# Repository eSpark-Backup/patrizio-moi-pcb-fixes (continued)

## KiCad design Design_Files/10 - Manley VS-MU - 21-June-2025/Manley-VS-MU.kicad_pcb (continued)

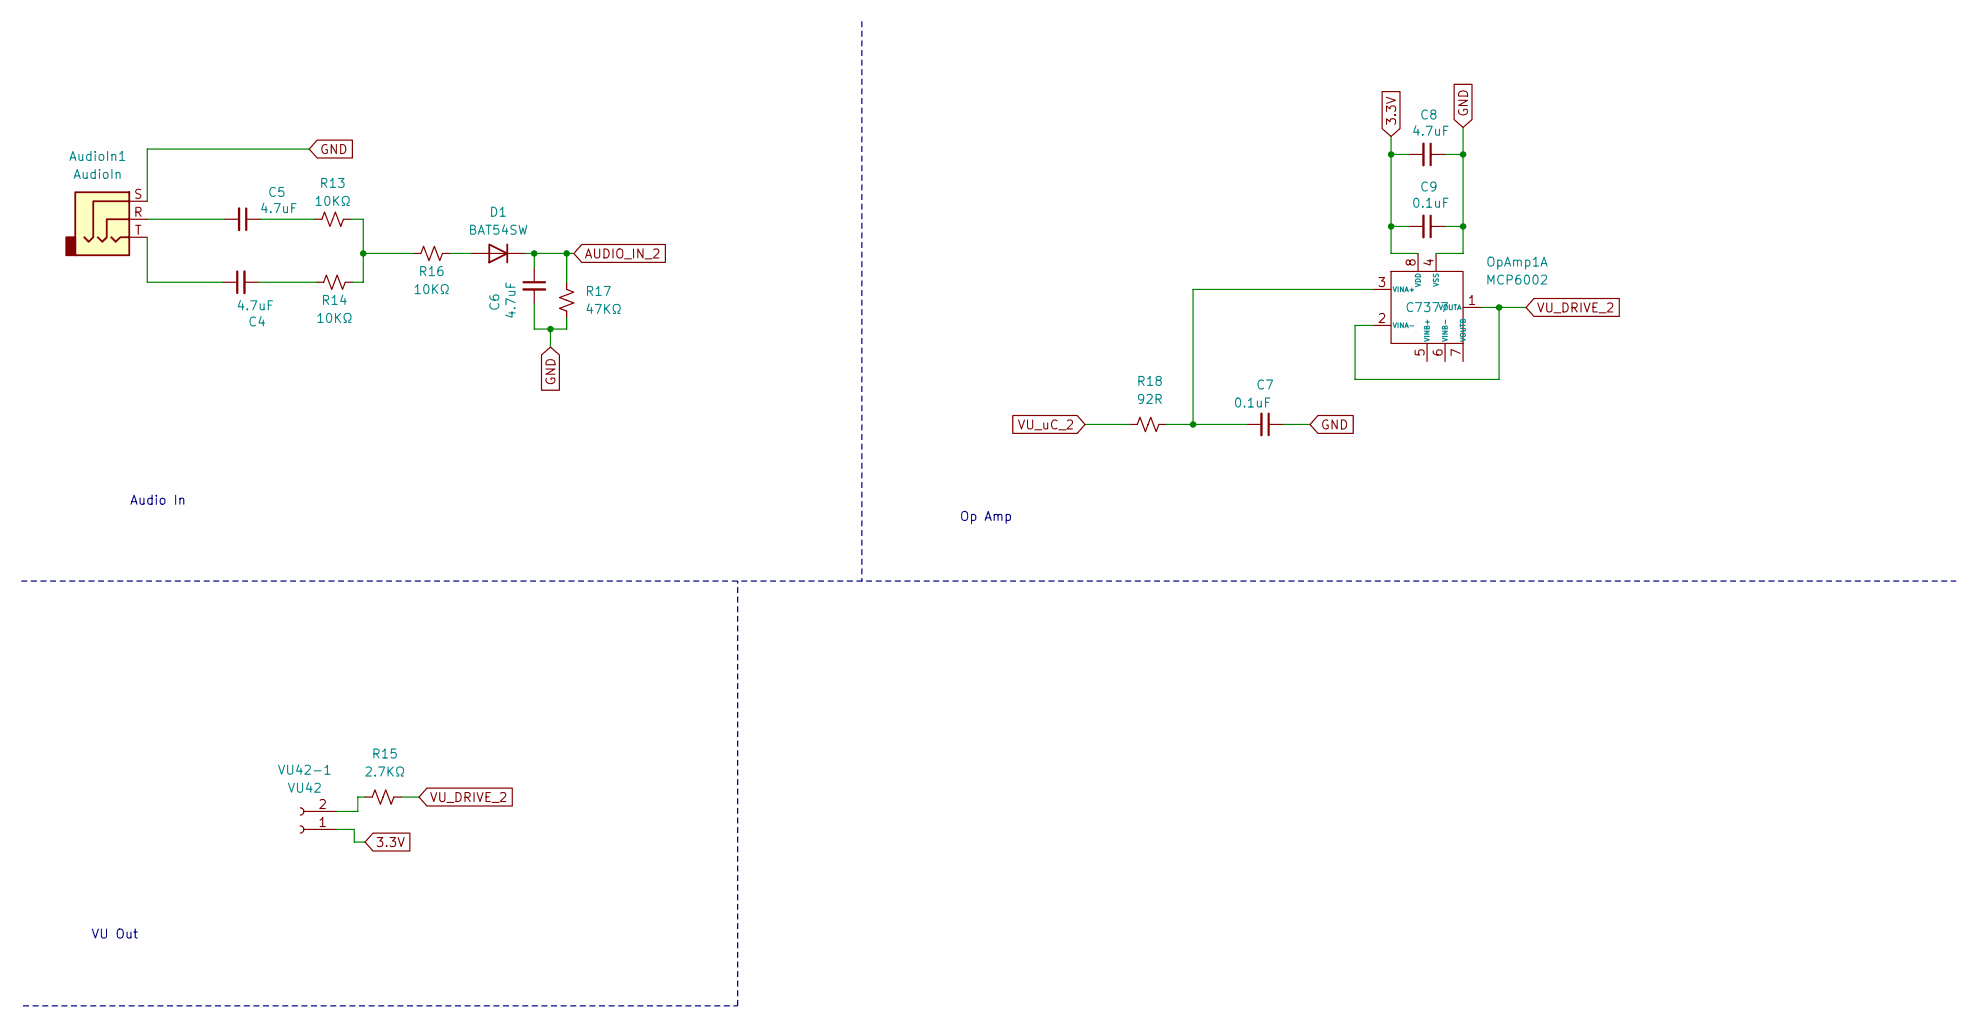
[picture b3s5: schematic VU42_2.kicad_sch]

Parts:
AudioIn1: AudioIn; Jack_3.5mm_PJ320D_Horizontal; LCSC Part Number C22459515
C4, C5, C6, C8: 4.7uF; C_0402_1005Metric; LCSC Part Number C23733
C7: 0.1uF; C_0402_1005Metric
C9: 0.1uF; C_0402_1005Metric; LCSC Part Number C1525
D1: BAT54SW; D_SOD-323; LCSC Part Number C27636114
OpAmp1: MCP6002; SOIC-8_3.9x4.9mm_P1.27mm; LCSC Part Number C7377
R13, R14, R16: 10KΩ; R_0402_1005Metric; LCSC Part Number C25744
R15: 2.7KΩ; R_0603_1608Metric; LCSC Part Number C13167
R17: 47KΩ; R_0402_1005Metric; LCSC Part Number C25792
R18: 92R; R_0402_1005Metric
VU42-1: VU42; PinSocket_1x02_P2.54mm_Vertical

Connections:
3.3V: C8.2, C9.2, OpAmp1.8 (VDD), VU42-1.1; also elsewhere on the board
AUDIO_IN_2: C6.1, D1.1 (K), R17.2; also elsewhere on the board
GND: AudioIn1.S, C6.2, C7.1, C8.1, C9.1, OpAmp1.4 (VSS), R17.1; also elsewhere on the board
unnamed: AudioIn1.R, C5.2
unnamed: AudioIn1.T, C4.1
unnamed: C4.2, R14.2
unnamed: C5.1, R13.2
unnamed: D1.2 (A), R16.1
unnamed: C7.2, OpAmp1.3 (VINA+), R18.1
unnamed: R13.1, R14.1, R16.2
unnamed: R15.2, VU42-1.2
VU_DRIVE_2: OpAmp1.1 (VOUTA), OpAmp1.2 (VINA-), R15.1
VU_uC_2: R18.2; also elsewhere on the board

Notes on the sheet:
VU Out
Op Amp
Audio In

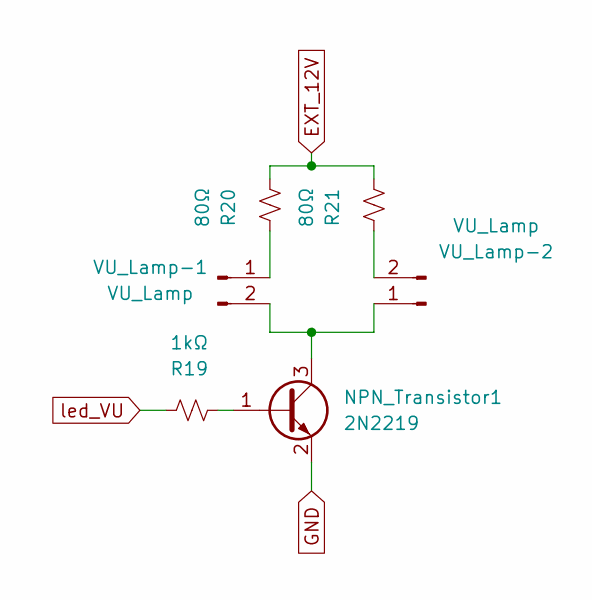
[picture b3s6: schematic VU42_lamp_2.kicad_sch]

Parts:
NPN_Transistor1: 2N2219; SOT-23; LCSC Part Number C2150
R19: 1kΩ; R_0402_1005Metric; Manufacturer_Part_Number 0402WGF3300TCE; LCSC Part Number C11702
R20, R21: 80Ω; R_0402_1005Metric; Manufacturer_Part_Number RT0402FRE0780RL; LCSC Part Number C854436
VU_Lamp-1, VU_Lamp-2: VU_Lamp; PinSocket_1x02_P2.54mm_Vertical

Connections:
EXT_12V: R20.1, R21.1; also elsewhere on the board
GND: NPN_Transistor1.2 (E); also elsewhere on the board
unnamed: NPN_Transistor1.1 (B), R19.1
unnamed: NPN_Transistor1.3 (C), VU_Lamp-1.2, VU_Lamp-2.1
unnamed: R20.2, VU_Lamp-1.1
unnamed: R21.2, VU_Lamp-2.2
led_VU: R19.2; also elsewhere on the board

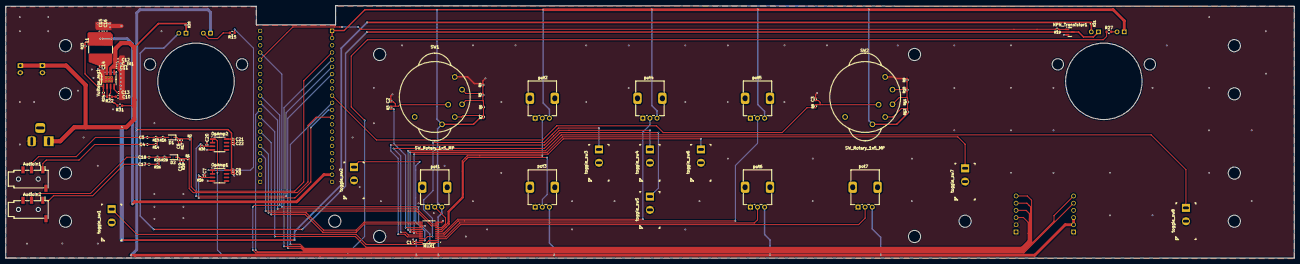
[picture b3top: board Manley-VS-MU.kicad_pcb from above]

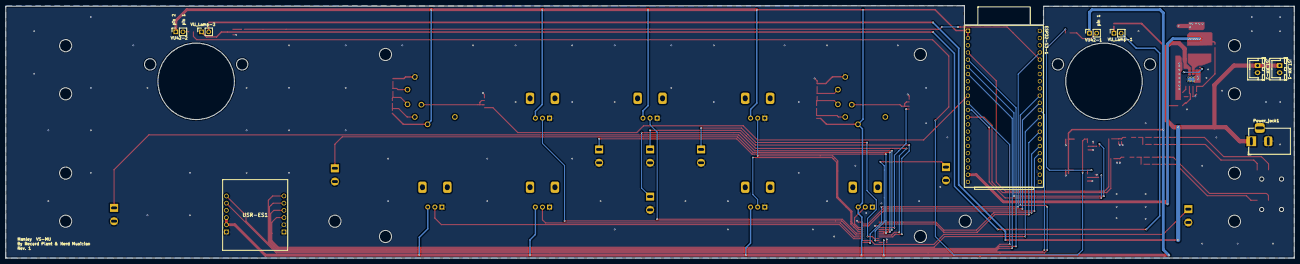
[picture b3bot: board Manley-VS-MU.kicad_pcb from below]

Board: 2 copper layers, 455.0 x 89.1 mm, 90 parts (9 on the bottom side), 76 nets.

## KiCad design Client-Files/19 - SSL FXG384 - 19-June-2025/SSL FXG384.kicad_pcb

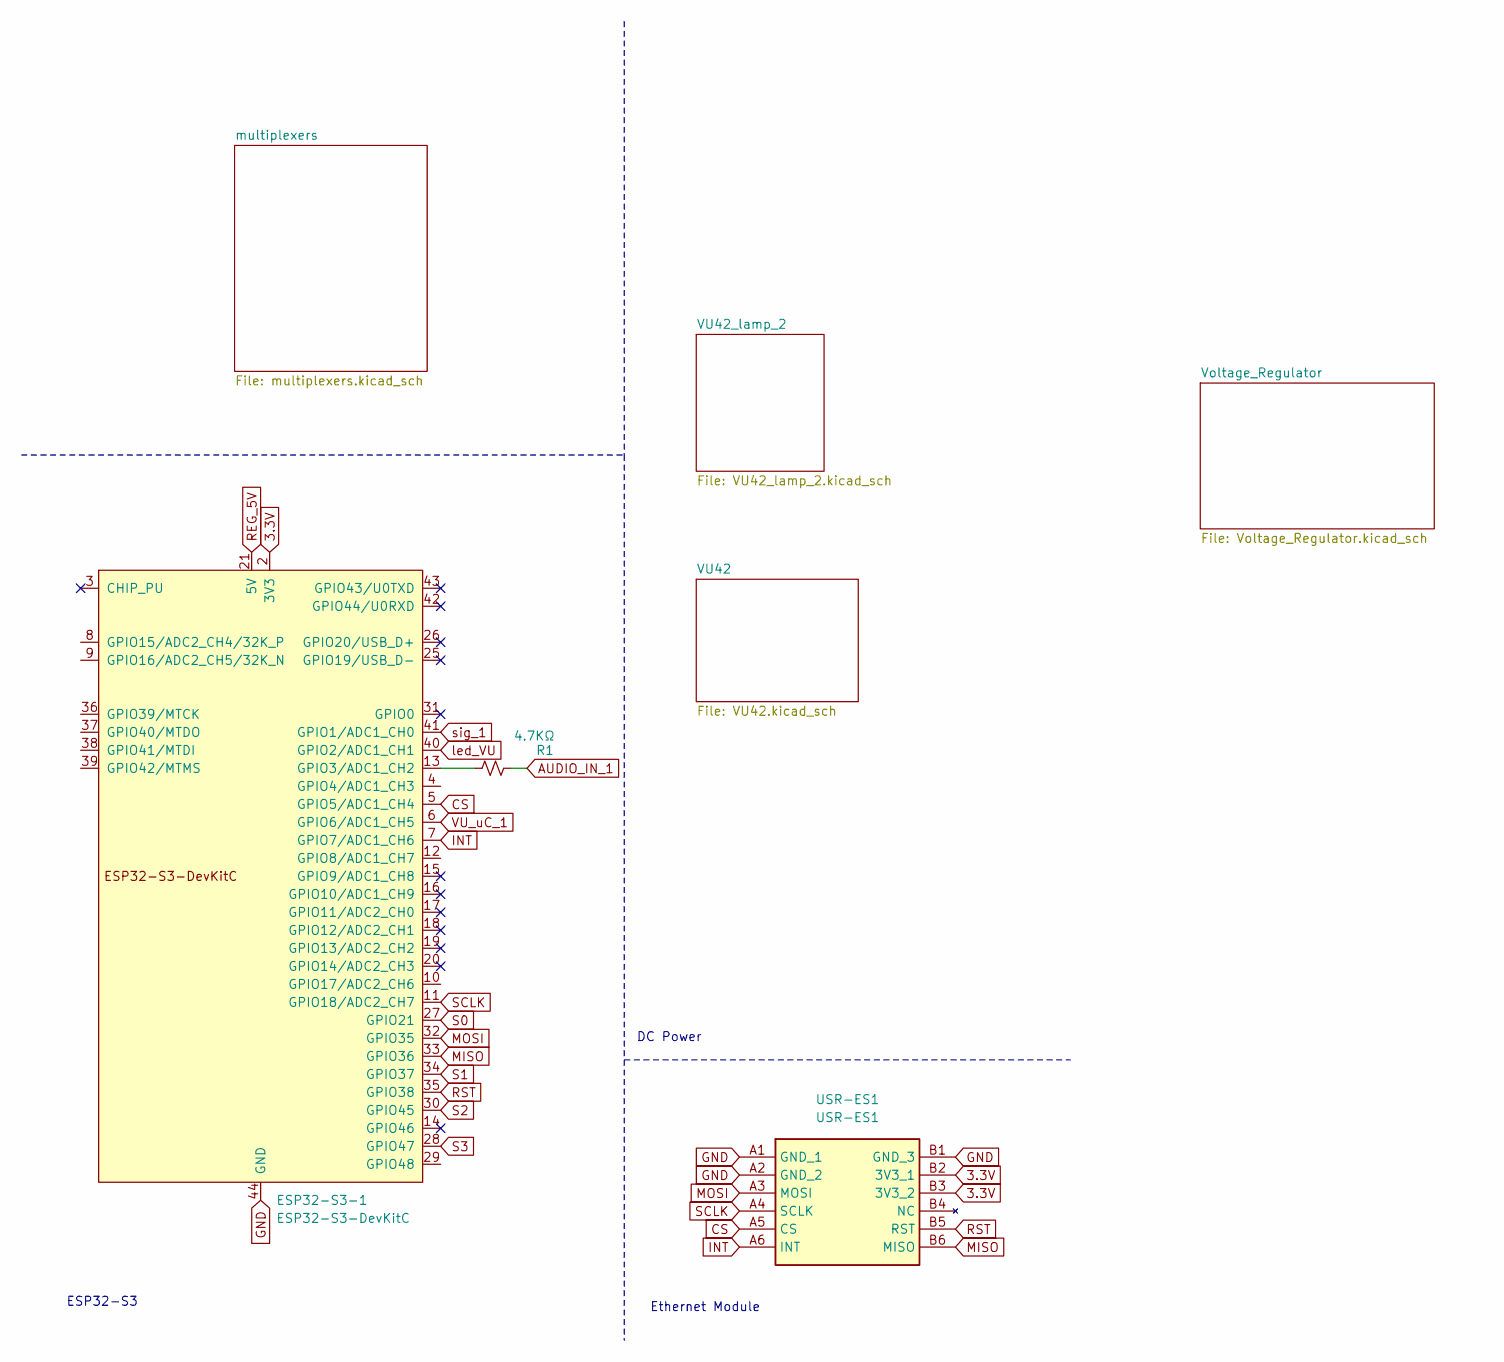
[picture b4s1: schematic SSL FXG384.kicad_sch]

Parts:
ESP32-S3-1: ESP32-S3-DevKitC; ESP32-S3-DEVKITC-1-N8R2-2
R1: 4.7KΩ; R_0402_1005Metric; LCSC Part Number C25900
USR-ES1: USR-ES1; USRES1; Manufacturer_Part_Number USR-ES1

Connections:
3.3V: ESP32-S3-1.1 (3V3), ESP32-S3-1.2 (3V3), USR-ES1.B2 (3V3_1), USR-ES1.B3 (3V3_2); also elsewhere on the board
AUDIO_IN_1: R1.1; also elsewhere on the board
CS: ESP32-S3-1.5 (GPIO5/ADC1_CH4), USR-ES1.A5 (CS)
GND: ESP32-S3-1.22 (GND), ESP32-S3-1.23 (GND), ESP32-S3-1.24 (GND), ESP32-S3-1.44 (GND), USR-ES1.A1 (GND_1), USR-ES1.A2 (GND_2), USR-ES1.B1 (GND_3); also elsewhere on the board
INT: ESP32-S3-1.7 (GPIO7/ADC1_CH6), USR-ES1.A6 (INT)
MISO: ESP32-S3-1.33 (GPIO36), USR-ES1.B6 (MISO)
MOSI: ESP32-S3-1.32 (GPIO35), USR-ES1.A3 (MOSI)
unnamed: ESP32-S3-1.13 (GPIO3/ADC1_CH2), R1.2
REG_5V: ESP32-S3-1.21 (5V); also elsewhere on the board
RST: ESP32-S3-1.35 (GPIO38), USR-ES1.B5 (RST)
S0: ESP32-S3-1.27 (GPIO21); also elsewhere on the board
S1: ESP32-S3-1.34 (GPIO37); also elsewhere on the board
S2: ESP32-S3-1.30 (GPIO45); also elsewhere on the board
S3: ESP32-S3-1.28 (GPIO47); also elsewhere on the board
SCLK: ESP32-S3-1.11 (GPIO18/ADC2_CH7), USR-ES1.A4 (SCLK)
VU_uC_1: ESP32-S3-1.6 (GPIO6/ADC1_CH5); also elsewhere on the board
led_VU: ESP32-S3-1.40 (GPIO2/ADC1_CH1); also elsewhere on the board
sig_1: ESP32-S3-1.41 (GPIO1/ADC1_CH0); also elsewhere on the board

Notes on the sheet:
Ethernet Module
DC Power
ESP32-S3

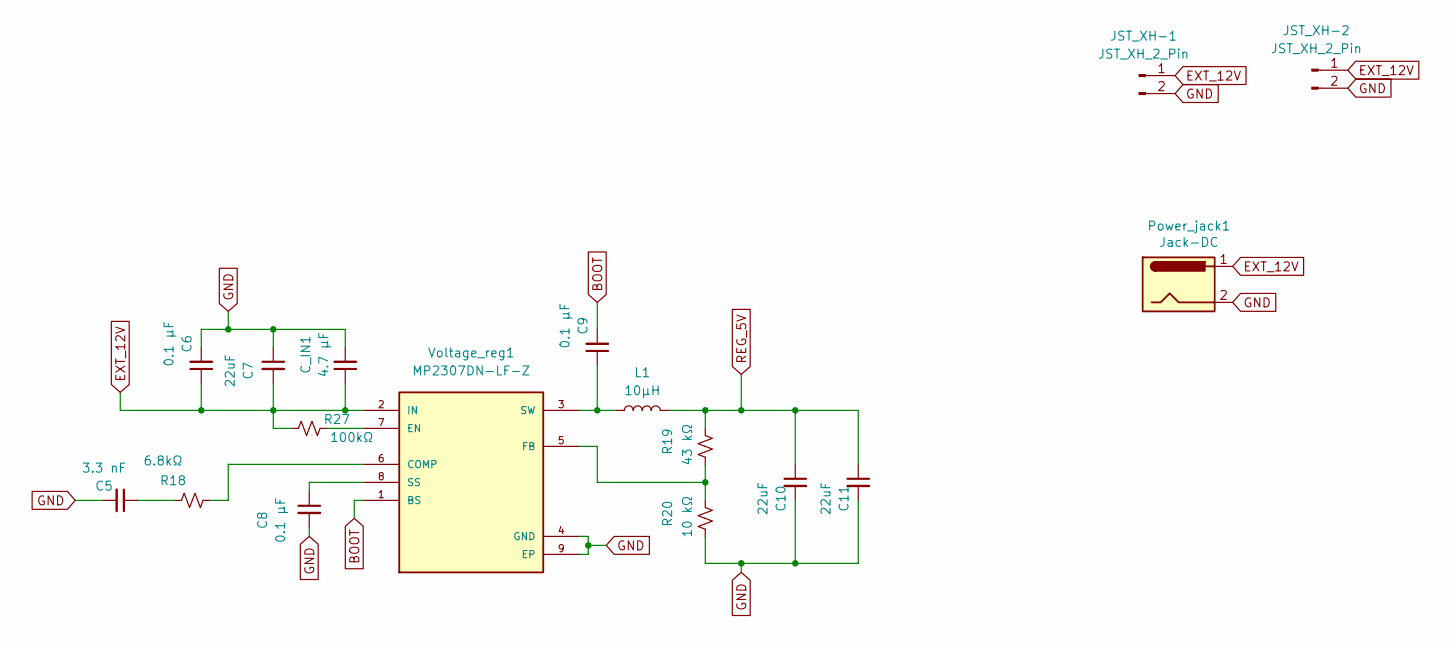
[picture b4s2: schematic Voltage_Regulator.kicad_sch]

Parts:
C5: 3.3 nF; C_0603_1608Metric; LCSC Part Number C1613
C6, C8, C9: 0.1 µF; C_0402_1005Metric; LCSC Part Number C1525
C7, C10, C11: 22uF; C_0603_1608Metric; LCSC Part Number C59461
C_IN1: 4.7 µF; C_0402_1005Metric; LCSC Part Number C23733
JST_XH-1, JST_XH-2: JST_XH_2_Pin; JST_XH_B2B-XH-A_1x02_P2.50mm_Vertical
L1: 10µH; L_Bourns-SRN8040_8x8.15mm; LCSC Part Number C37429
Power_jack1: Jack-DC; BarrelJack_Horizontal
R18: 6.8kΩ; R_0603_1608Metric; LCSC Part Number C23212
R19: 43 kΩ; R_0402_1005Metric; LCSC Part Number C2906943
R20: 10 kΩ; R_0402_1005Metric; LCSC Part Number C25744
R27: 100kΩ; R_0603_1608Metric
Voltage_reg1: MP2307DN-LF-Z; SOIC-8-1EP_3.9x4.9mm_P1.27mm_EP2.29x3mm_ThermalVias; PARTREV 1.9; LCSC Part Number C2928813

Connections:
BOOT: C9.2, Voltage_reg1.1 (BS)
EXT_12V: C6.1, C7.2, C_IN1.1, JST_XH-1.1, JST_XH-2.1, Power_jack1.1, R27.1, Voltage_reg1.2 (IN); also elsewhere on the board
GND: C5.2, C6.2, C7.1, C8.2, C10.2, C11.2, C_IN1.2, JST_XH-1.2, JST_XH-2.2, Power_jack1.2, R20.2, Voltage_reg1.4 (GND), Voltage_reg1.9 (EP); also elsewhere on the board
unnamed: C5.1, R18.1
unnamed: R18.2, Voltage_reg1.6 (COMP)
unnamed: R27.2, Voltage_reg1.7 (EN)
unnamed: R19.2, R20.1, Voltage_reg1.5 (FB)
unnamed: C8.1, Voltage_reg1.8 (SS)
unnamed: C9.1, L1.1, Voltage_reg1.3 (SW)
REG_5V: C10.1, C11.1, L1.2, R19.1; also elsewhere on the board

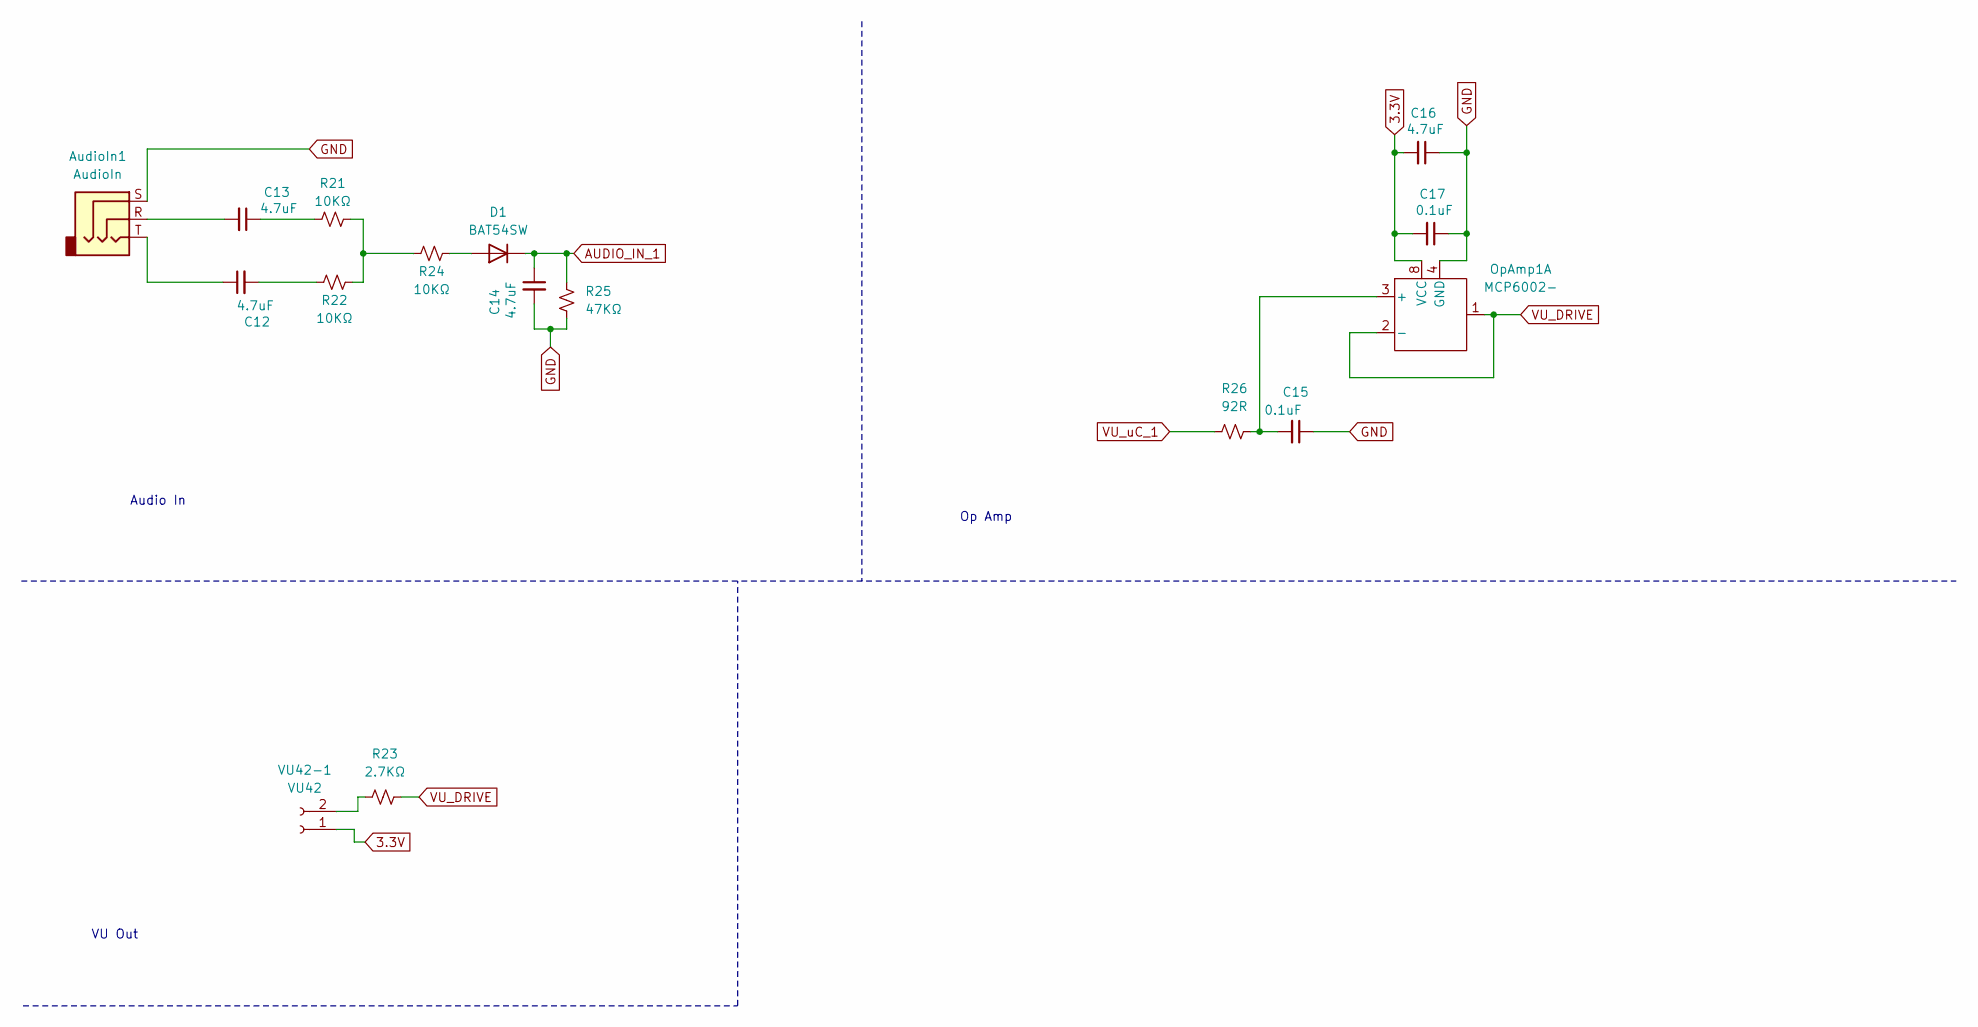
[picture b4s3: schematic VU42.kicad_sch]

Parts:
AudioIn1: AudioIn; Jack_3.5mm_PJ320D_Horizontal; LCSC Part Number C22459515
C12, C13, C14, C16: 4.7uF; C_0402_1005Metric; LCSC Part Number C23733
C15: 0.1uF; C_0402_1005Metric
C17: 0.1uF; C_0402_1005Metric; LCSC Part Number C1525
D1: BAT54SW; D_SOD-323; LCSC Part Number C27636114
OpAmp1: MCP6002-; SOIC-8_3.9x4.9mm_P1.27mm; LCSC Part Number C7377
R21, R22, R24: 10KΩ; R_0402_1005Metric; LCSC Part Number C25744
R23: 2.7KΩ; R_0603_1608Metric; LCSC Part Number C13167
R25: 47KΩ; R_0402_1005Metric; LCSC Part Number C25792
R26: 92R; R_0402_1005Metric
VU42-1: VU42; PinSocket_1x02_P2.54mm_Vertical

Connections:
3.3V: C16.2, C17.2, OpAmp1.8 (VCC), VU42-1.1; also elsewhere on the board
AUDIO_IN_1: C14.1, D1.1 (K), R25.2; also elsewhere on the board
GND: AudioIn1.S, C14.2, C15.1, C16.1, C17.1, OpAmp1.4 (GND), R25.1; also elsewhere on the board
unnamed: AudioIn1.R, C13.2
unnamed: AudioIn1.T, C12.1
unnamed: C12.2, R22.2
unnamed: C13.1, R21.2
unnamed: D1.2 (A), R24.1
unnamed: C15.2, OpAmp1.3 (+), R26.1
unnamed: R21.1, R22.1, R24.2
unnamed: R23.2, VU42-1.2
VU_DRIVE: OpAmp1.1, OpAmp1.2 (-), R23.1
VU_uC_1: R26.2; also elsewhere on the board

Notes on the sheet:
VU Out
Op Amp
Audio In

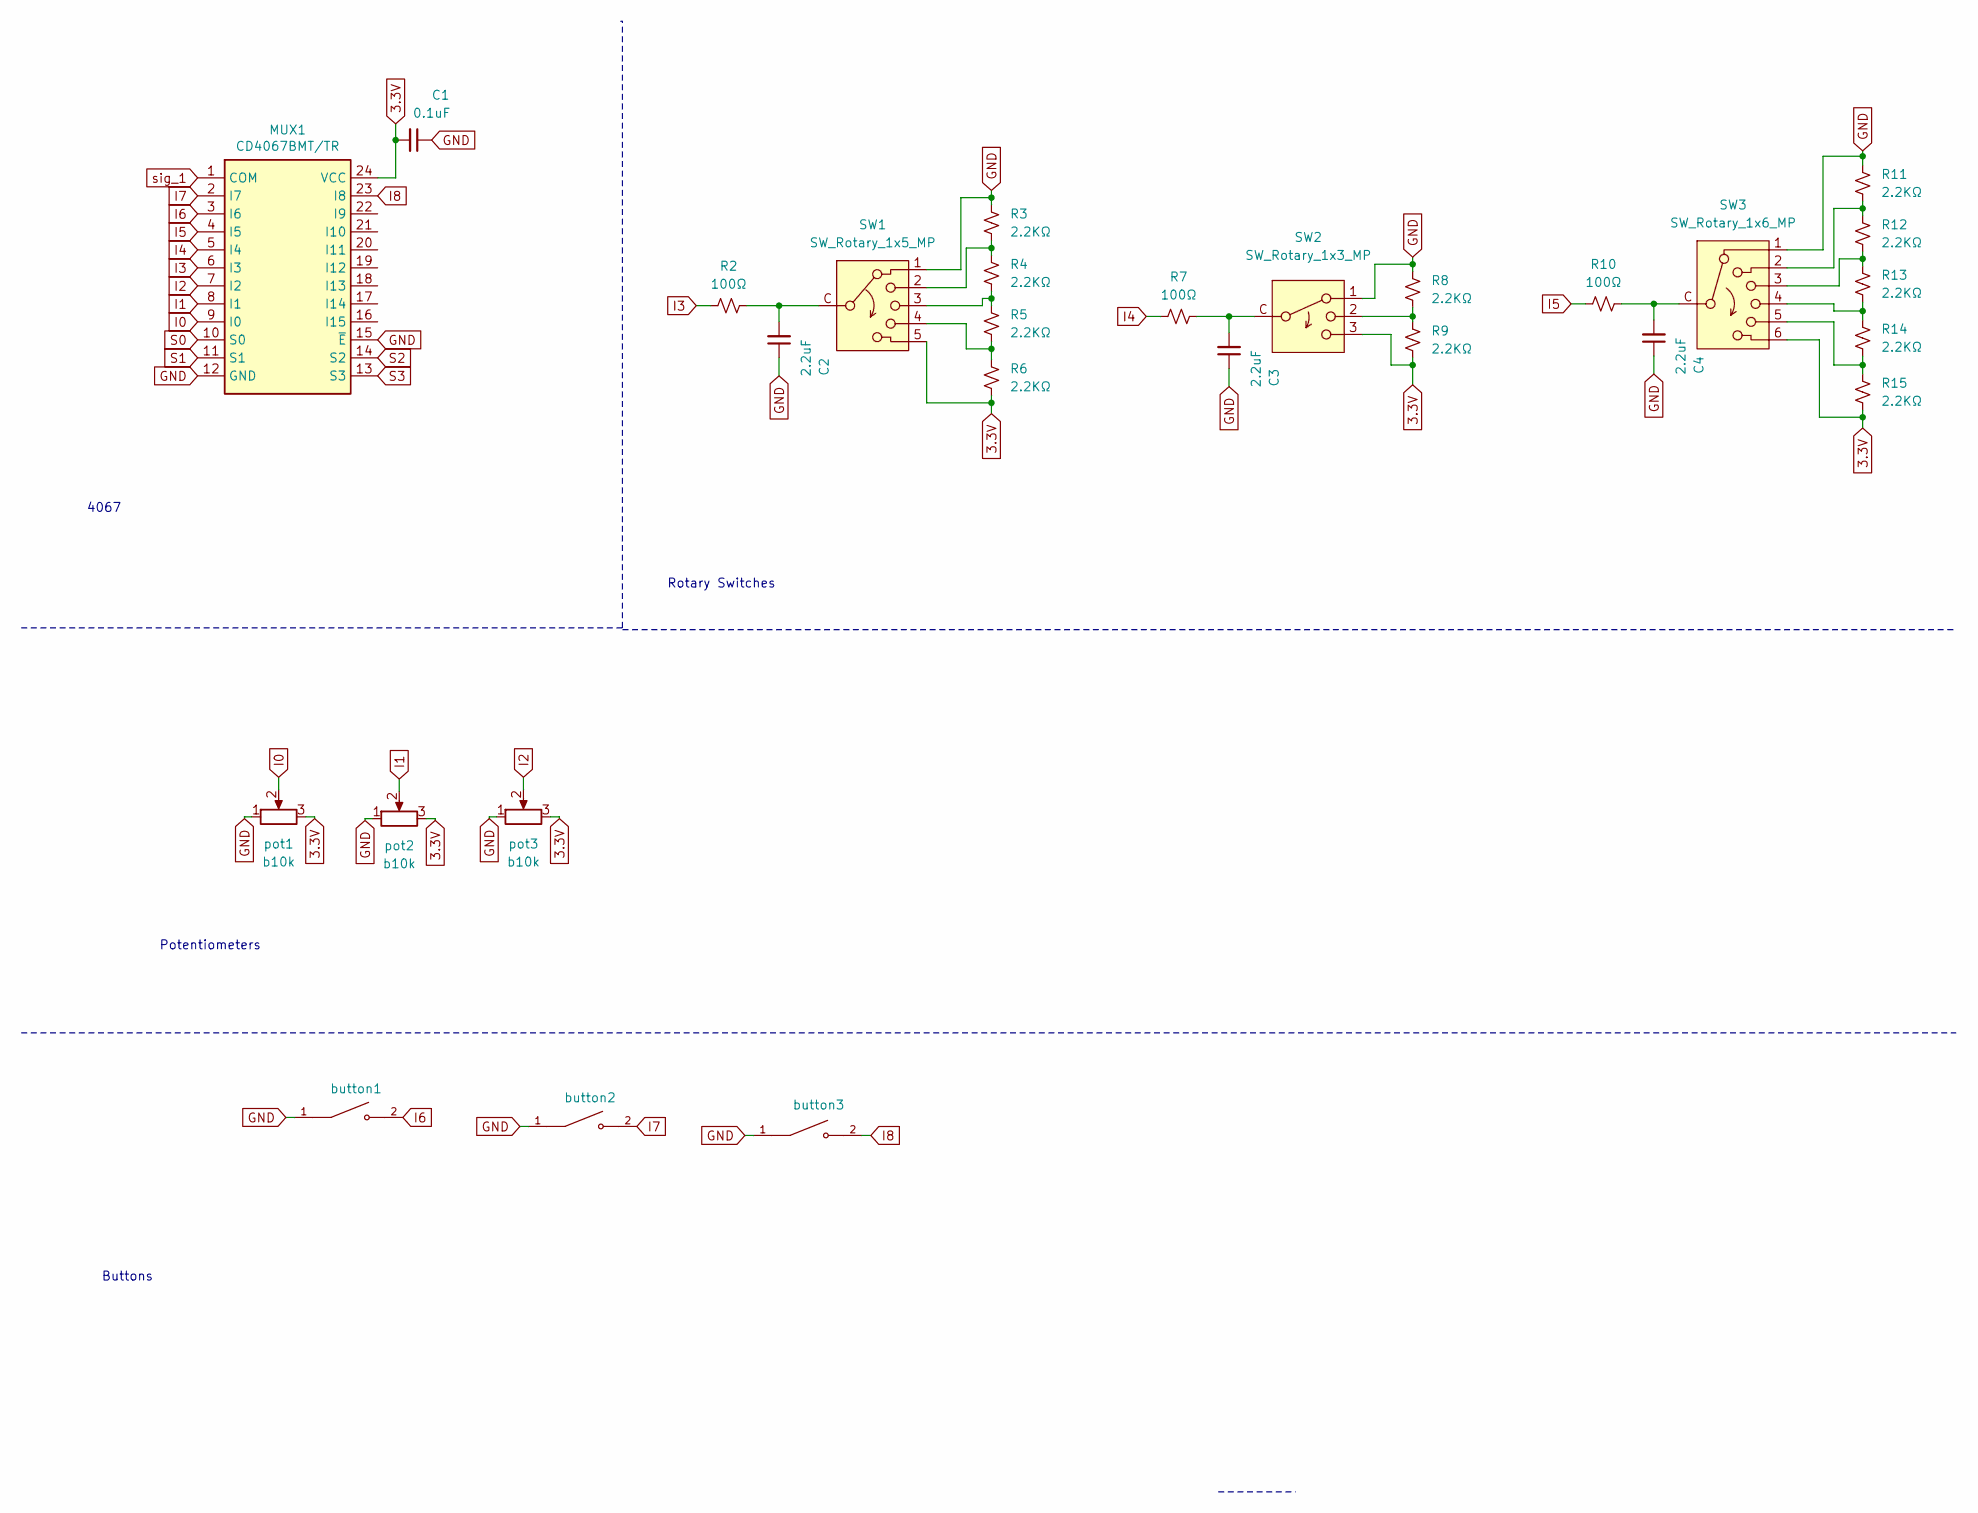
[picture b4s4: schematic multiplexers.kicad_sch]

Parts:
C1: 0.1uF; C_0402_1005Metric; LCSC Part Number C14663
C2, C3, C4: 2.2uF; C_0402_1005Metric; LCSC Part Number C12530
MUX1: CD4067BMT/TR; TSSOP-24_4.4x7.8mm_P0.65mm; LCSC Part Number C7432333
R2, R7, R10: 100Ω; R_0402_1005Metric; LCSC Part Number C25076
R3, R4, R5, R6, R8, R9, R11, R12, R13, R14, R15: 2.2KΩ; R_0402_1005Metric; LCSC Part Number C25879
SW1: SW_Rotary_1x5_MP; SW_Rotary_RS25-5P
SW2: SW_Rotary_1x3_MP; SW_Rotary_RS25-3P
SW3: SW_Rotary_1x6_MP; SW_Rotary_RS25-6P
button1, button2, button3: bttn; SW_TL2285EE; PARTREV B
pot1, pot2, pot3: b10k; Potentiometer_Alps_RK09K_Single_Vertical

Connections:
3.3V: C1.2, MUX1.24 (VCC), R6.1, R9.1, R15.1, SW1.5, SW2.3, SW3.6, pot1.3, pot2.3, pot3.3; also elsewhere on the board
GND: C1.1, C2.1, C3.1, C4.1, MUX1.12 (GND), MUX1.15 (~E), R3.2, R8.2, R11.2, SW1.1, SW2.1, SW3.1, button1.1, button2.1, button3.1, pot1.1, pot2.1, pot3.1; also elsewhere on the board
I0: MUX1.9 (I0), pot1.2
I1: MUX1.8 (I1), pot2.2
I2: MUX1.7 (I2), pot3.2
I3: MUX1.6 (I3), R2.1
I4: MUX1.5 (I4), R7.1
I5: MUX1.4 (I5), R10.1
I6: MUX1.3 (I6), button1.2
I7: MUX1.2 (I7), button2.2
I8: MUX1.23 (I8), button3.2
unnamed: C2.2, R2.2, SW1.C
unnamed: C3.2, R7.2, SW2.C
unnamed: C4.2, R10.2, SW3.C
unnamed: R3.1, R4.2, SW1.2
unnamed: R4.1, R5.2, SW1.3
unnamed: R5.1, R6.2, SW1.4
unnamed: R8.1, R9.2, SW2.2
unnamed: R11.1, R12.2, SW3.2
unnamed: R12.1, R13.2, SW3.3
unnamed: R13.1, R14.2, SW3.4
unnamed: R14.1, R15.2, SW3.5
S0: MUX1.10 (S0); also elsewhere on the board
S1: MUX1.11 (S1); also elsewhere on the board
S2: MUX1.14 (S2); also elsewhere on the board
S3: MUX1.13 (S3); also elsewhere on the board
sig_1: MUX1.1 (COM); also elsewhere on the board

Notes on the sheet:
4067
Potentiometers
Buttons
Rotary Switches

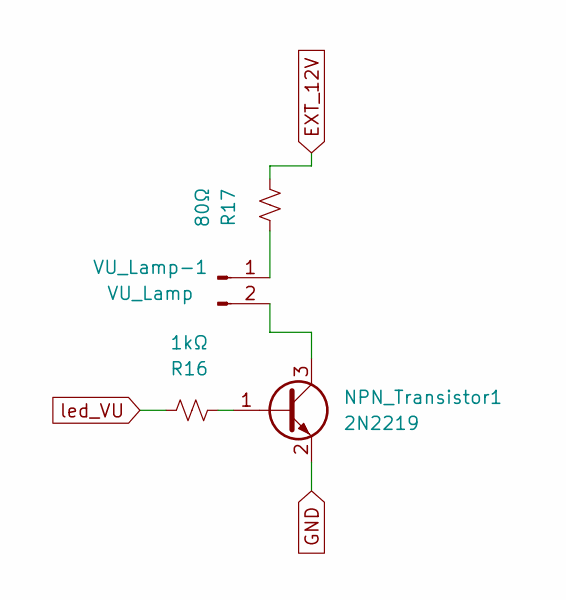
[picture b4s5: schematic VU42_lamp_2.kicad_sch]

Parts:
NPN_Transistor1: 2N2219; SOT-23; LCSC Part Number C2150
R16: 1kΩ; R_0402_1005Metric; Manufacturer_Part_Number 0402WGF3300TCE; LCSC Part Number C11702
R17: 80Ω; R_0402_1005Metric; Manufacturer_Part_Number RT0402FRE0780RL; LCSC Part Number C854436
VU_Lamp-1: VU_Lamp; PinSocket_1x02_P2.54mm_Vertical

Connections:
EXT_12V: R17.1; also elsewhere on the board
GND: NPN_Transistor1.2 (E); also elsewhere on the board
unnamed: NPN_Transistor1.1 (B), R16.1
unnamed: NPN_Transistor1.3 (C), VU_Lamp-1.2
unnamed: R17.2, VU_Lamp-1.1
led_VU: R16.2; also elsewhere on the board

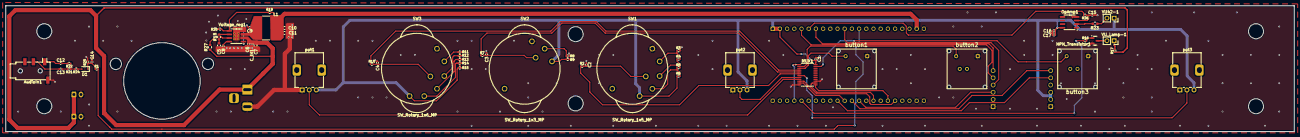
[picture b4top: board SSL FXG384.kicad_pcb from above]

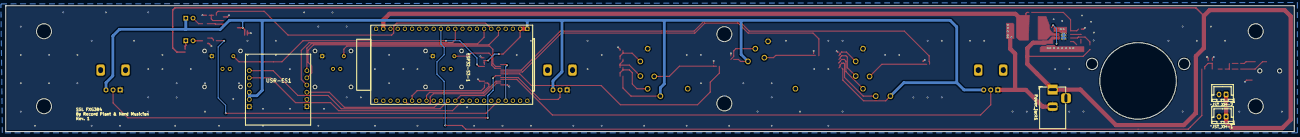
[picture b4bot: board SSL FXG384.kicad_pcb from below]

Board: 2 copper layers, 454.7 x 44.4 mm, 68 parts (5 on the bottom side), 58 nets.

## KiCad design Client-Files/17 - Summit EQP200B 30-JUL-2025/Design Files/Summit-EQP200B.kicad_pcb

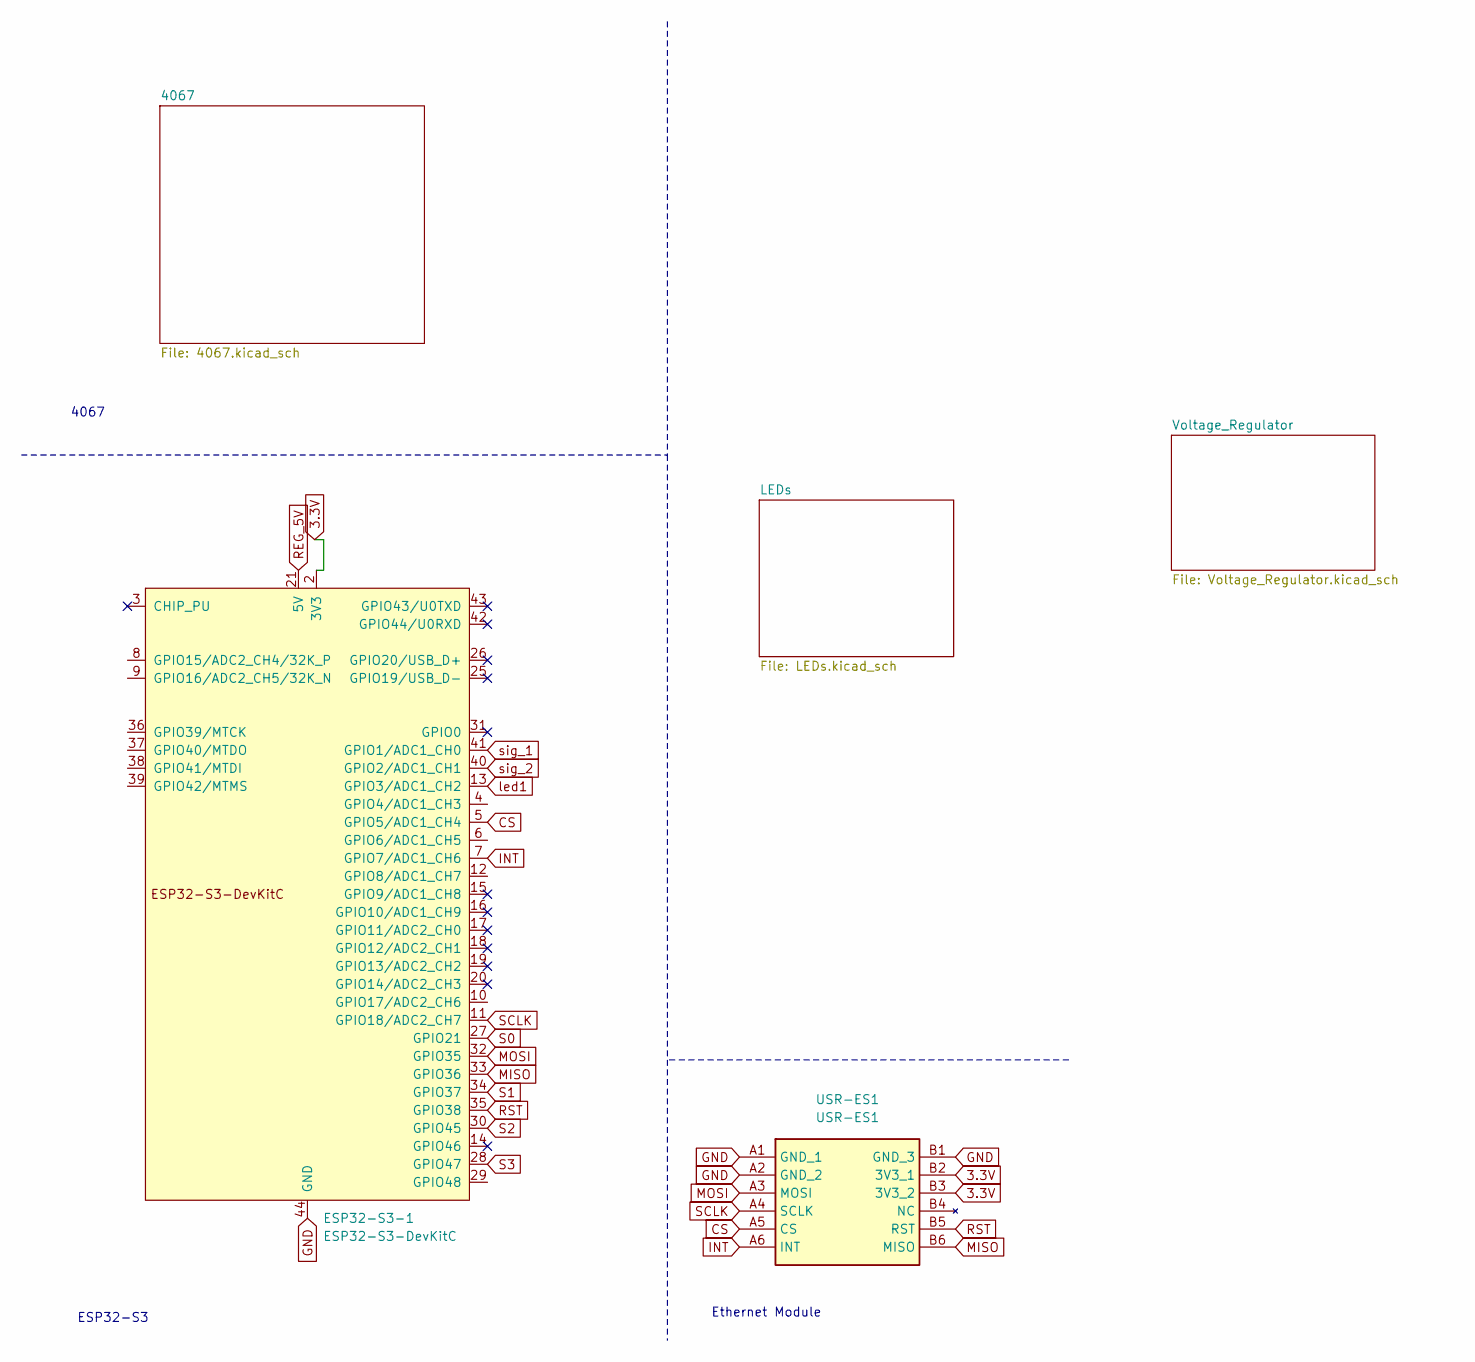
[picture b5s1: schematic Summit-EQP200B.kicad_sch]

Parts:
ESP32-S3-1: ESP32-S3-DevKitC; ESP32-S3-DEVKITC-1-N8R2-2
USR-ES1: USR-ES1; USRES1; Manufacturer_Part_Number USR-ES1

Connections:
3.3V: ESP32-S3-1.1 (3V3), ESP32-S3-1.2 (3V3), USR-ES1.B2 (3V3_1), USR-ES1.B3 (3V3_2); also elsewhere on the board
CS: ESP32-S3-1.5 (GPIO5/ADC1_CH4), USR-ES1.A5 (CS)
GND: ESP32-S3-1.22 (GND), ESP32-S3-1.23 (GND), ESP32-S3-1.24 (GND), ESP32-S3-1.44 (GND), USR-ES1.A1 (GND_1), USR-ES1.A2 (GND_2), USR-ES1.B1 (GND_3); also elsewhere on the board
INT: ESP32-S3-1.7 (GPIO7/ADC1_CH6), USR-ES1.A6 (INT)
MISO: ESP32-S3-1.33 (GPIO36), USR-ES1.B6 (MISO)
MOSI: ESP32-S3-1.32 (GPIO35), USR-ES1.A3 (MOSI)
REG_5V: ESP32-S3-1.21 (5V); also elsewhere on the board
RST: ESP32-S3-1.35 (GPIO38), USR-ES1.B5 (RST)
S0: ESP32-S3-1.27 (GPIO21); also elsewhere on the board
S1: ESP32-S3-1.34 (GPIO37); also elsewhere on the board
S2: ESP32-S3-1.30 (GPIO45); also elsewhere on the board
S3: ESP32-S3-1.28 (GPIO47); also elsewhere on the board
SCLK: ESP32-S3-1.11 (GPIO18/ADC2_CH7), USR-ES1.A4 (SCLK)
led1: ESP32-S3-1.13 (GPIO3/ADC1_CH2); also elsewhere on the board
sig_1: ESP32-S3-1.41 (GPIO1/ADC1_CH0); also elsewhere on the board
sig_2: ESP32-S3-1.40 (GPIO2/ADC1_CH1); also elsewhere on the board

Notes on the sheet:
Ethernet Module
ESP32-S3
4067

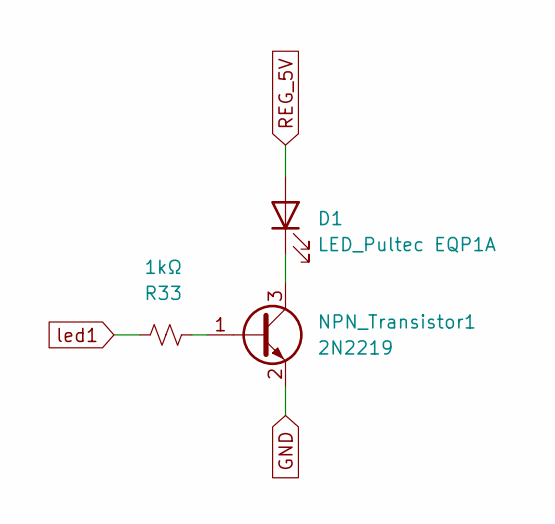
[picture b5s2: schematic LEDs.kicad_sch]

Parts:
D1: LED_Pultec EQP1A; LED_Pultech_1
NPN_Transistor1: 2N2219; SOT-23; LCSC Part Number C2150
R33: 1kΩ; R_0402_1005Metric; Manufacturer_Part_Number 0402WGF3300TCE; LCSC Part Number C11702

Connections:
GND: NPN_Transistor1.2 (E); also elsewhere on the board
unnamed: D1.1 (K), NPN_Transistor1.3 (C)
unnamed: NPN_Transistor1.1 (B), R33.1
REG_5V: D1.2 (A); also elsewhere on the board
led1: R33.2; also elsewhere on the board
